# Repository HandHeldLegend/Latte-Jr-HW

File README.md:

# Latte Project
This is the official Github page for project Latte Jr from Hand Held Legend.

## Software and PCB License
<br />This firmware and PCB model are licensed under a <a rel="license" href="http://creativecommons.org/licenses/by-nc-sa/3.0/">Creative Commons Attribution-NonCommercial-ShareAlike 3.0 Unported License</a>.

## 3D Models License

<br />The 3D shell, buttons, and other associated models are licensed under a <a rel="license" href="http://creativecommons.org/licenses/by/4.0/">Creative Commons Attribution 4.0 International License</a>.

## Attributions

Resources Cross-Referenced for shell shape:
- 3D Scans by Wesk

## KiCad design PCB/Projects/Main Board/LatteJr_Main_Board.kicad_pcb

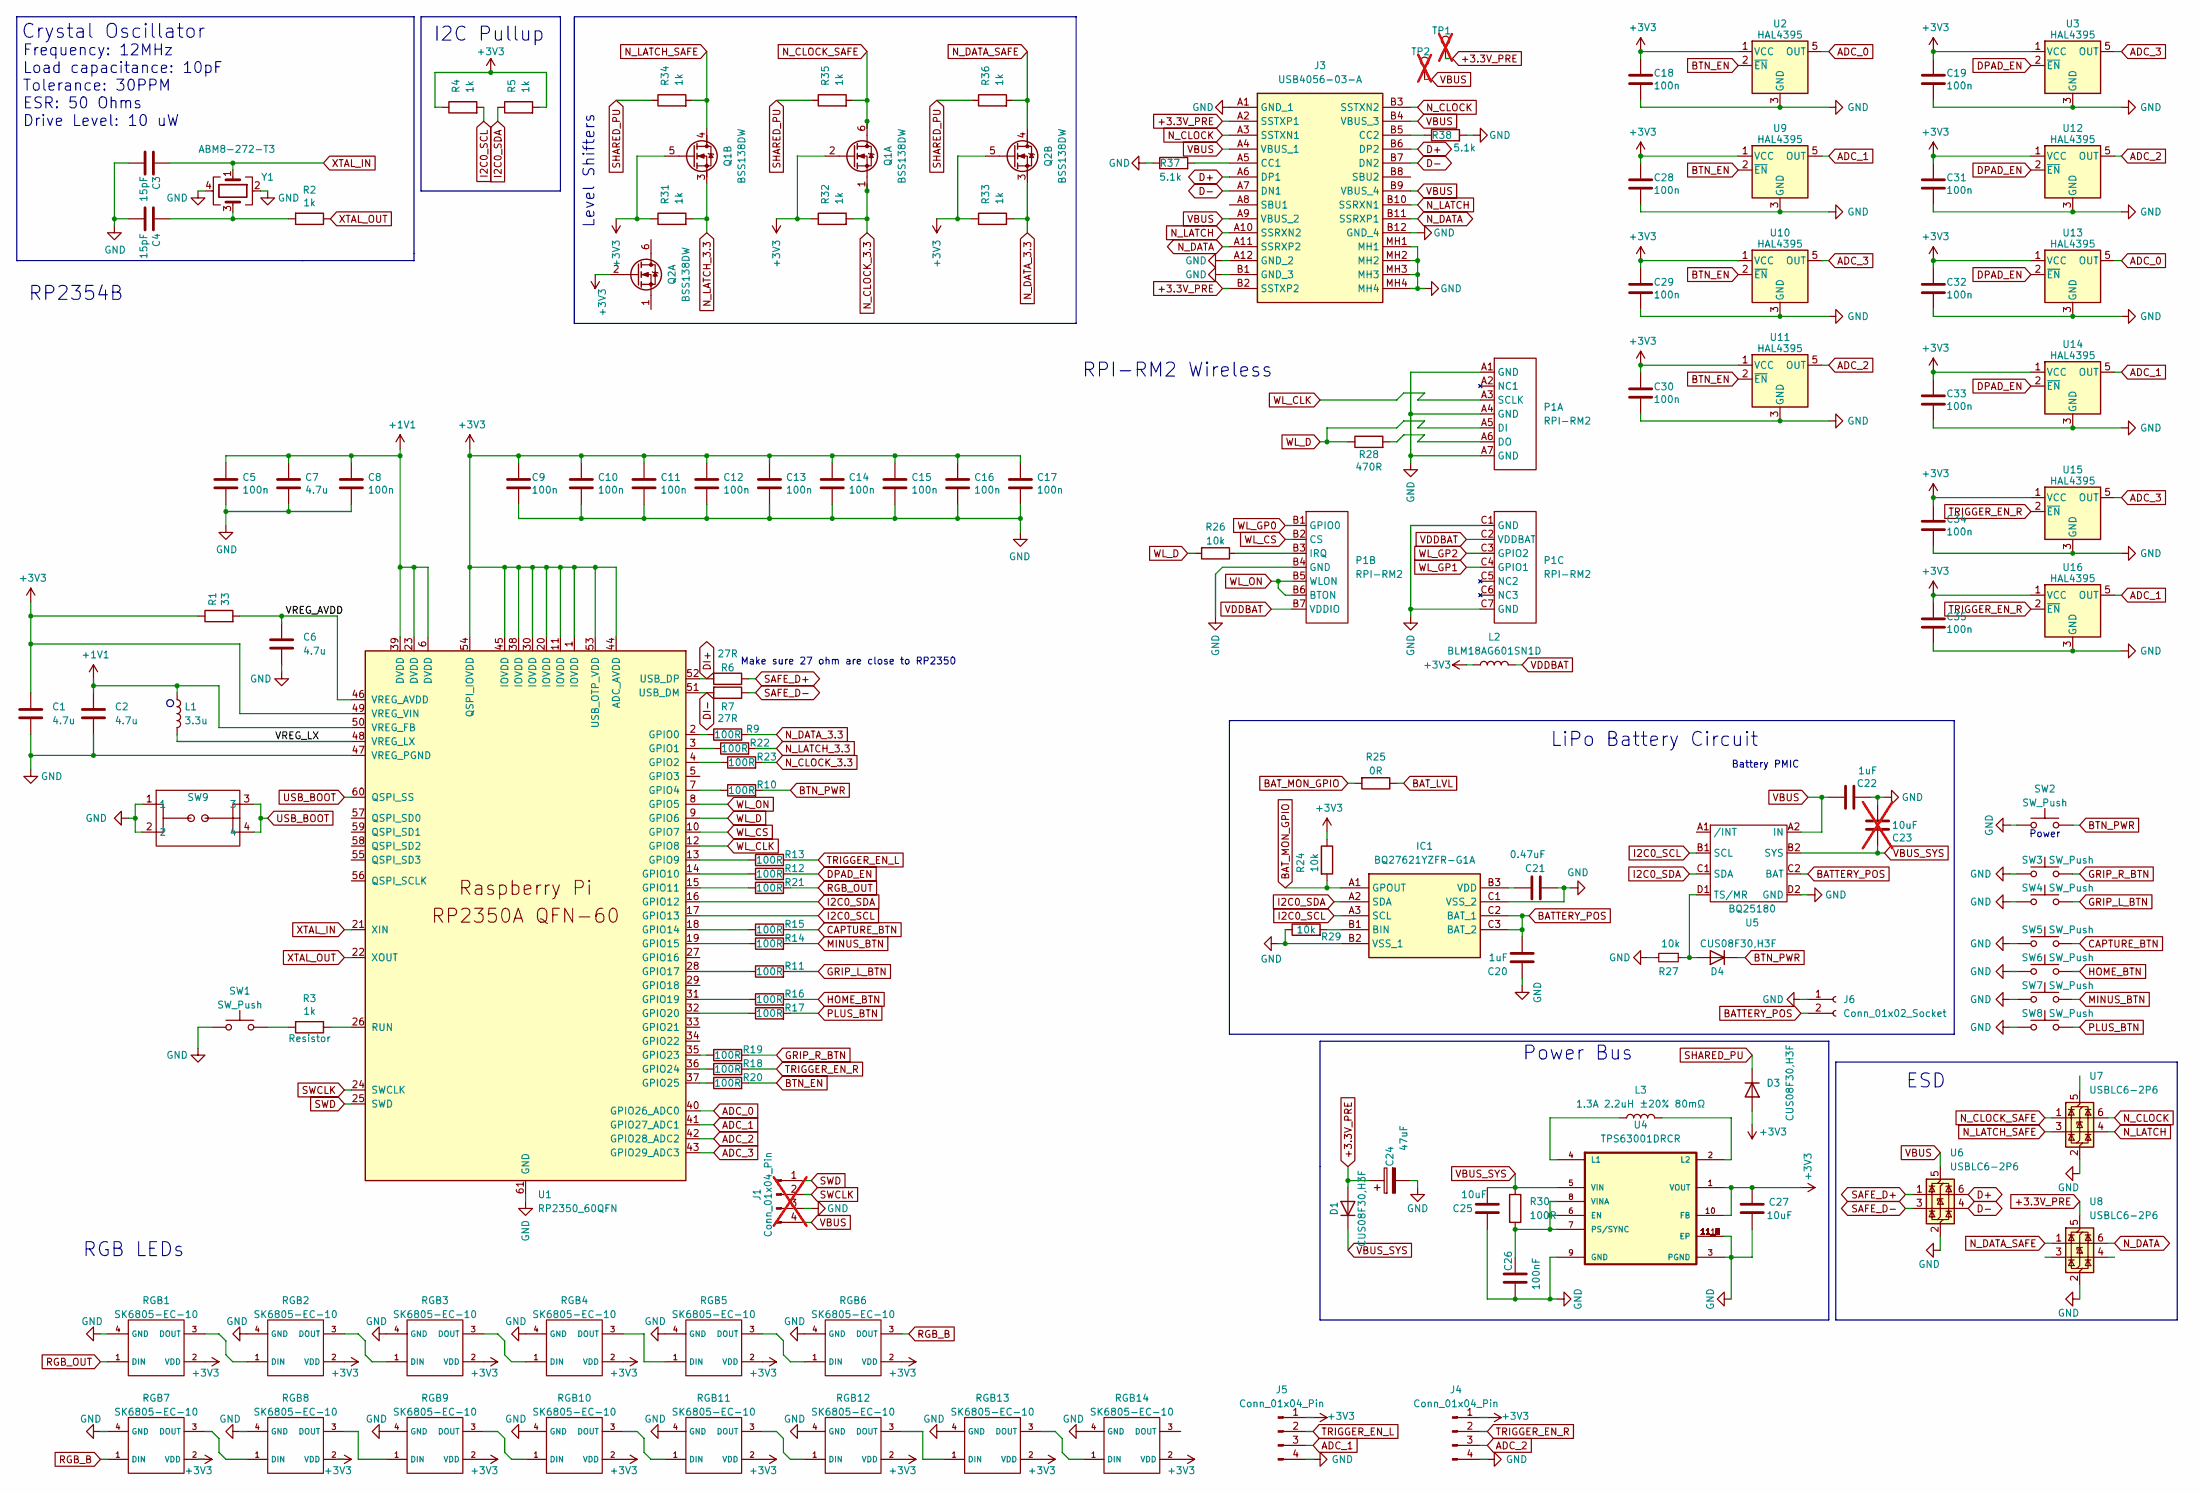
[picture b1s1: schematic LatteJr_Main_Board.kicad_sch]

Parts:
C1, C2, C6, C7: 4.7u; C_0402_1005Metric; MPN CL05A475KP5NRNC; LCSC C368809
C3, C4: 15pF; C_0402_1005Metric; MPN CC0402FRNPO9BN150; LCSC C326803
C5, C8, C9, C10, C11, C12, C13, C14, C15, C16, C17, C18, C19, C28, C29, C30, C31, C32, C33, C34, C35: 100n; C_0201_0603Metric; MPN GRM033R61A104KE15D; LCSC C76934
C20, C22: 1uF; C_0201_0603Metric; MPN GRM033R60J105KEA2D; LCSC C76929
C21: 0.47uF; C_0201_0603Metric; MPN GRM033R60J474KE90D; LCSC C85926
C23: 10uF; C_0805_2012Metric; MPN CL21A106KPFNNNE; LCSC C17024; not fitted
C24: 47uF; CP_EIA-3216-18_Kemet-A; MPN TAJA476K006RNJ; LCSC C7190
C25, C27: 10uF; C_0805_2012Metric; MPN CL21A106KPFNNNE; LCSC C17024
C26: 100nF; C_0201_0603Metric; MPN CL03A104KQ3NNNC; LCSC C160831
D1, D3, D4: CUS08F30,H3F; D_SOD-323_HandSoldering; MPN CUS08F30,H3F; LCSC C150183
IC1: BQ27621YZFR-G1A; BGA9C50P3X3_162X158X62; Mouser Part Number 595-BQ27621YZFR-G1A
J1: Conn_01x04_Pin; PinHeader_1x04_P2.00mm_Vertical; not fitted
J3: USB4056-03-A; USB405603A; Mouser Part Number 640-USB4056-03-A
J4, J5: Conn_01x04_Pin; 5051100492; MPN 5051100492; LCSC C588007
J6: Conn_01x02_Socket; Molex_PicoBlade_53048-0210_1x02_P1.25mm_Horizontal; MPN 530480210; LCSC C505099
L1: 3.3u; L_pol_2016; MPN AOTA-B201610S3R3-101-T; LCSC C42411119
L2: BLM18AG601SN1D; L_0603_1608Metric; MPN BLM18AG601SN1D; LCSC C19330
L3: 1.3A 2.2uH ±20% 80mΩ; L_1008_2520Metric; MPN MIP25202R2MBE; LCSC C315721
P1: RPI-RM2; RPI_RM2; MPN RPI-RM2
Q1, Q2: BSS138DW; SOT-363_SC-70-6; MPN BSS138DW-7-F; LCSC C154900
R1: 33; R_0201_0603Metric; MPN RC0201FR-0733RL; LCSC C295794
R2, R3, R4, R5, R31, R32, R33, R34, R35, R36: 1k; R_0201_0603Metric; MPN RC0201FR-071KL; LCSC C138165
R6, R7: 27R; R_0201_0603Metric; MPN RC0201FR-0727RL; LCSC C273268
R9, R10, R11, R12, R13, R14, R15, R16, R17, R18, R19, R20, R21, R22, R23, R30: 100R; R_0201_0603Metric; MPN RC0201FR-07100RL; LCSC C77623
R24, R26, R27, R29: 10k; R_0201_0603Metric; MPN RC0201FR-0710KL; LCSC C106225
R25: 0R; R_0201_0603Metric; MPN RC0201FR-070RL; LCSC C106227
R28: 470R; R_0201_0603Metric; MPN AC0201FR-07470RL; LCSC C226558
R37, R38: 5.1k; R_0201_0603Metric; MPN RC0201FR-075K1L; LCSC C274341
RGB1, RGB2, RGB3, RGB4, RGB5, RGB6, RGB7, RGB8, RGB9, RGB10, RGB11, RGB12, RGB13, RGB14: SK6805-EC-10; MPN SK6805-EC-10; LCSC C22394946
SW1, SW2, SW3, SW4, SW5, SW6, SW7, SW8: SW_Push; KSC-TE; MPN KSC201J LFS; LCSC C221725
SW9: 1TS026A-1000-0550; MPN 1TS026A-1000-0550; LCSC C913778
TP1, TP2: TestPoint; TestPoint_Pad_D1.0mm; not fitted
U1: RP2350_60QFN; RP2350-QFN-60-1EP_7x7_P0.4mm_EP3.4x3.4mm_ThermalVias; MPN RP2354A; LCSC C41378174
U2, U3, U9, U10, U11, U12, U13, U14, U15, U16: HAL4395; SOT-23-5L; MPN HAL4395SO5; LCSC C49165022
U4: TPS63001DRCR; VREG_V62_16624-01YE; MPN TPS63001DRCR; LCSC C28060
U5: BQ25180; DSBGA; MPN BQ25180YBGR; LCSC C3682423
U6, U7, U8: USBLC6-2P6; SOT-666; MPN USBLC6-2P6; LCSC C2827693
Y1: ABM8-272-T3; Crystal_SMD_3225-4Pin_3.2x2.5mm; MPN ABM8-272-T3; LCSC C20625731

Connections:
+1V1: C2.1, C5.1, C7.1, C8.1, L1.1, U1.6 (DVDD), U1.23 (DVDD), U1.39 (DVDD), U1.50 (VREG_FB)
+3.3V_PRE: C24.1, D1.2 (A), J3.A2 (SSTXP1), J3.B2 (SSTXP2), TP1.1, U8.5 (VBUS)
+3V3: C1.1, C9.1, C10.1, C11.1, C12.1, C13.1, C14.1, C15.1, C16.1, C17.1, C18.1, C19.1, C27.1, C28.1, C29.1, C30.1, C31.1, C32.1, C33.1, C34.1, C35.1, D3.2 (A), J4.1, J5.1, L2.1, Q1.2 (G1), Q1.5 (G2), Q2.2 (G1), Q2.5 (G2), R1.1, R4.1, R5.2, R24.1, R31.1, R32.1, R33.1, RGB1.2 (VDD), RGB2.2 (VDD), RGB3.2 (VDD), RGB4.2 (VDD), RGB5.2 (VDD), RGB6.2 (VDD), RGB7.2 (VDD), RGB8.2 (VDD), RGB9.2 (VDD), RGB10.2 (VDD), RGB11.2 (VDD), RGB12.2 (VDD), RGB13.2 (VDD), RGB14.2 (VDD), U1.1 (IOVDD), U1.11 (IOVDD), U1.20 (IOVDD), U1.30 (IOVDD), U1.38 (IOVDD), U1.44 (ADC_AVDD), U1.45 (IOVDD), U1.49 (VREG_VIN), U1.53 (USB_OTP_VDD), U1.54 (QSPI_IOVDD), U2.1 (VCC), U3.1 (VCC), U4.1 (VOUT), U4.10 (FB), U9.1 (VCC), U10.1 (VCC), U11.1 (VCC), U12.1 (VCC), U13.1 (VCC), U14.1 (VCC), U15.1 (VCC), U16.1 (VCC)
/VREG_AVDD: C6.1, R1.2, U1.46 (VREG_AVDD)
/VREG_LX: L1.2, U1.48 (VREG_LX)
ADC_0: U1.40 (GPIO26_ADC0), U2.5 (OUT), U13.5 (OUT)
ADC_1: J5.3, U1.41 (GPIO27_ADC1), U9.5 (OUT), U14.5 (OUT), U16.5 (OUT)
ADC_2: J4.3, U1.42 (GPIO28_ADC2), U11.5 (OUT), U12.5 (OUT)
ADC_3: U1.43 (GPIO29_ADC3), U3.5 (OUT), U10.5 (OUT), U15.5 (OUT)
BATTERY_POS: C20.2, IC1.C2 (BAT_1), IC1.C3 (BAT_2), J6.2, U5.C2 (BAT)
BAT_LVL: R25.1
BAT_MON_GPIO: IC1.A1 (GPOUT), R24.2, R25.2
BTN_EN: R20.2, U2.2 (~EN), U9.2 (~EN), U10.2 (~EN), U11.2 (~EN)
BTN_PWR: D4.1 (K), R10.2, SW2.2
CAPTURE_BTN: R15.2, SW5.2
D+: J3.A6 (DP1), J3.B6 (DP2), U6.6 (I/O1)
D-: J3.A7 (DN1), J3.B7 (DN2), U6.4 (I/O2)
DI+: R6.2, U1.52 (USB_DP)
DI-: R7.2, U1.51 (USB_DM)
DPAD_EN: R12.2, U3.2 (~EN), U12.2 (~EN), U13.2 (~EN), U14.2 (~EN)
GND: C1.2, C2.2, C3.2, C4.2, C5.2, C6.2, C7.2, C8.2, C9.2, C10.2, C11.2, C12.2, C13.2, C14.2, C15.2, C16.2, C17.2, C18.2, C19.2, C20.1, C21.2, C22.2, C23.1, C24.2, C25.1, C26.1, C27.2, C28.2, C29.2, C30.2, C31.2, C32.2, C33.2, C34.2, C35.2, IC1.B2 (VSS_1), IC1.C1 (VSS_2), J1.3, J3.A1 (GND_1), J3.A12 (GND_2), J3.B1 (GND_3), J3.B12 (GND_4), J3.MH1, J3.MH2, J3.MH3, J3.MH4, J4.4, J5.4, J6.1, P1.A1 (GND), P1.A4 (GND), P1.A7 (GND), P1.B4 (GND), P1.C1 (GND), P1.C7 (GND), R27.2, R29.1, R37.1, R38.2, RGB1.4 (GND), RGB2.4 (GND), RGB3.4 (GND), RGB4.4 (GND), RGB5.4 (GND), RGB6.4 (GND), RGB7.4 (GND), RGB8.4 (GND), RGB9.4 (GND), RGB10.4 (GND), RGB11.4 (GND), RGB12.4 (GND), RGB13.4 (GND), RGB14.4 (GND), SW1.1, SW2.1, SW3.1, SW4.1, SW5.1, SW6.1, SW7.1, SW8.1, SW9.1, SW9.2, U1.47 (VREG_PGND), U1.61 (GND), U2.3 (GND), U3.3 (GND), U4.3 (PGND), U4.9 (GND), U4.11 (EP), U4.11_1 (EP), U4.11_2 (EP), U4.11_3 (EP), U4.11_4 (EP), U4.11_5 (EP), U4.11_6 (EP), U4.11_7 (EP), U4.11_8 (EP), U5.D2 (GND), U6.2 (GND), U7.2 (GND), U8.2 (GND), U9.3 (GND), U10.3 (GND), U11.3 (GND), U12.3 (GND), U13.3 (GND), U14.3 (GND), U15.3 (GND), U16.3 (GND), Y1.2, Y1.4
GRIP_L_BTN: R11.2, SW4.2
GRIP_R_BTN: R19.2, SW3.2
HOME_BTN: R16.2, SW6.2
I2C0_SCL: IC1.A3 (SCL), R4.2, U1.17 (GPIO13), U5.B1 (SCL)
I2C0_SDA: IC1.A2 (SDA), R5.1, U1.16 (GPIO12), U5.C1 (SDA)
MINUS_BTN: R14.2, SW7.2
N_CLOCK: J3.A3 (SSTXN1), J3.B3 (SSTXN2), U7.6 (I/O1)
N_CLOCK_3.3: Q1.1 (S1), R23.2, R32.2
N_CLOCK_SAFE: Q1.6 (D1), R35.2, U7.1 (I/O1)
N_DATA: J3.A11 (SSRXP2), J3.B11 (SSRXP1), U8.6 (I/O1)
N_DATA_3.3: Q2.3 (D2), R9.2, R33.2
N_DATA_SAFE: Q2.4 (S2), R36.2, U8.1 (I/O1)
N_LATCH: J3.A10 (SSRXN2), J3.B10 (SSRXN1), U7.4 (I/O2)
N_LATCH_3.3: Q1.3 (D2), R22.2, R31.2
N_LATCH_SAFE: Q1.4 (S2), R34.2, U7.3 (I/O2)
unnamed: C4.1, R2.2, Y1.3
unnamed: D4.2 (A), R27.1, U5.D1 (TS/MR)
unnamed: IC1.B1 (BIN), R29.2
unnamed: C21.1, IC1.B3 (VDD)
unnamed: J3.A5 (CC1), R37.2
unnamed: J3.B5 (CC2), R38.1
unnamed: P1.A6 (DO), R28.2
unnamed: P1.B3 (IRQ), R26.1
unnamed: R3.2, SW1.2
unnamed: RGB1.3 (DOUT), RGB2.1 (DIN)
unnamed: RGB2.3 (DOUT), RGB3.1 (DIN)
unnamed: RGB3.3 (DOUT), RGB4.1 (DIN)
unnamed: RGB4.3 (DOUT), RGB5.1 (DIN)
unnamed: RGB5.3 (DOUT), RGB6.1 (DIN)
unnamed: RGB7.3 (DOUT), RGB8.1 (DIN)
unnamed: RGB8.3 (DOUT), RGB9.1 (DIN)
unnamed: RGB9.3 (DOUT), RGB10.1 (DIN)
unnamed: RGB10.3 (DOUT), RGB11.1 (DIN)
unnamed: RGB11.3 (DOUT), RGB12.1 (DIN)
unnamed: RGB12.3 (DOUT), RGB13.1 (DIN)
unnamed: RGB13.3 (DOUT), RGB14.1 (DIN)
unnamed: R9.1, U1.2 (GPIO0)
unnamed: R22.1, U1.3 (GPIO1)
unnamed: R23.1, U1.4 (GPIO2)
unnamed: R10.1, U1.7 (GPIO4)
unnamed: R13.1, U1.13 (GPIO9)
unnamed: R12.1, U1.14 (GPIO10)
unnamed: R21.1, U1.15 (GPIO11)
unnamed: R15.1, U1.18 (GPIO14)
unnamed: R14.1, U1.19 (GPIO15)
unnamed: R11.1, U1.28 (GPIO17)
unnamed: R16.1, U1.31 (GPIO19)
unnamed: R17.1, U1.32 (GPIO20)
unnamed: R19.1, U1.35 (GPIO23)
unnamed: R18.1, U1.36 (GPIO24)
unnamed: R20.1, U1.37 (GPIO25)
unnamed: R3.1, U1.26 (RUN)
unnamed: C26.2, R30.2, U4.6 (EN), U4.7 (PS/SYNC), U4.8 (VINA)
unnamed: L3.1, U4.4 (L1)
unnamed: L3.2, U4.2 (L2)
PLUS_BTN: R17.2, SW8.2
RGB_B: RGB6.3 (DOUT), RGB7.1 (DIN)
RGB_OUT: R21.2, RGB1.1 (DIN)
SAFE_D+: R6.1, U6.1 (I/O1)
SAFE_D-: R7.1, U6.3 (I/O2)
SHARED_PU: D3.1 (K), R34.1, R35.1, R36.1
SWCLK: J1.2, U1.24 (SWCLK)
SWD: J1.1, U1.25 (SWD)
TRIGGER_EN_L: J5.2, R13.2
TRIGGER_EN_R: J4.2, R18.2, U15.2 (~EN), U16.2 (~EN)
USB_BOOT: SW9.3, SW9.4, U1.60 (QSPI_SS)
VBUS: C22.1, J1.4, J3.A4 (VBUS_1), J3.A9 (VBUS_2), J3.B4 (VBUS_3), J3.B9 (VBUS_4), TP2.1, U5.A2 (IN), U6.5 (VBUS)
VBUS_SYS: C23.2, C25.2, D1.1 (K), R30.1, U4.5 (VIN), U5.B2 (SYS)
VDDBAT: L2.2, P1.B7 (VDDIO), P1.C2 (VDDBAT)
WL_CLK: P1.A3 (SCLK), U1.12 (GPIO8)
WL_CS: P1.B2 (CS), U1.10 (GPIO7)
WL_D: P1.A5 (DI), R26.2, R28.1, U1.9 (GPIO6)
WL_GP0: P1.B1 (GPIO0)
WL_GP1: P1.C4 (GPIO1)
WL_GP2: P1.C3 (GPIO2)
WL_ON: P1.B5 (WLON), P1.B6 (BTON), U1.8 (GPIO5)
XTAL_IN: C3.1, U1.21 (XIN), Y1.1
XTAL_OUT: R2.1, U1.22 (XOUT)

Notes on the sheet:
Power
ESD
RP2354B
RGB LEDs
RPI-RM2 Wireless
Crystal Oscillator
Level Shifters
I2C Pullup
Frequency: 12MHz Load capacitance: 10pF Tolerance: 30PPM ESR: 50 Ohms Drive Level: 10 uW
Power Bus
Make sure 27 ohm are close to RP2350
Battery PMIC
LiPo Battery Circuit

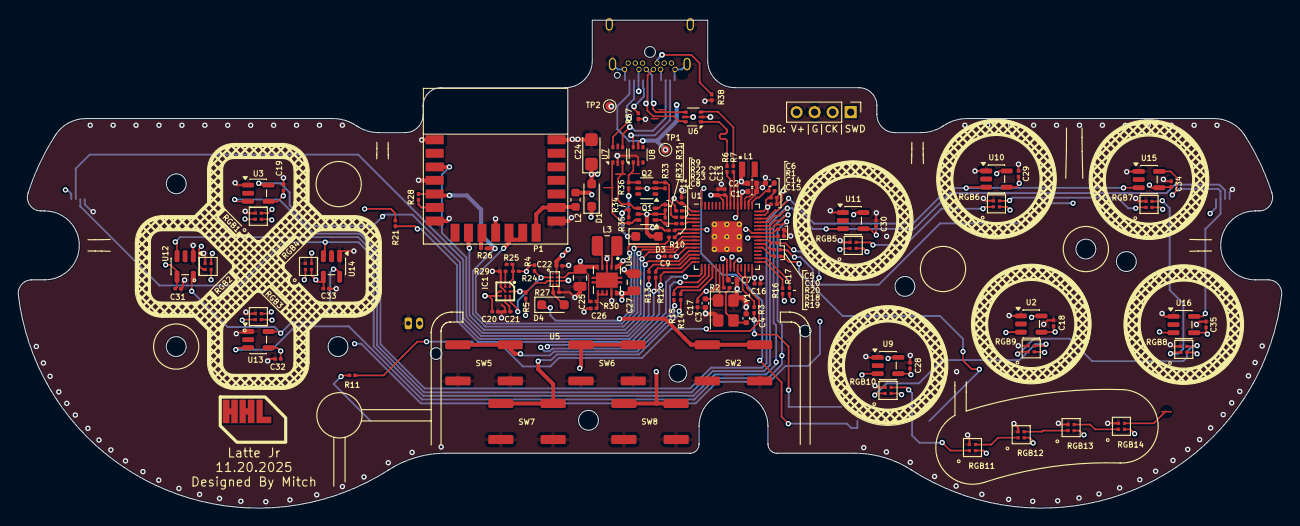
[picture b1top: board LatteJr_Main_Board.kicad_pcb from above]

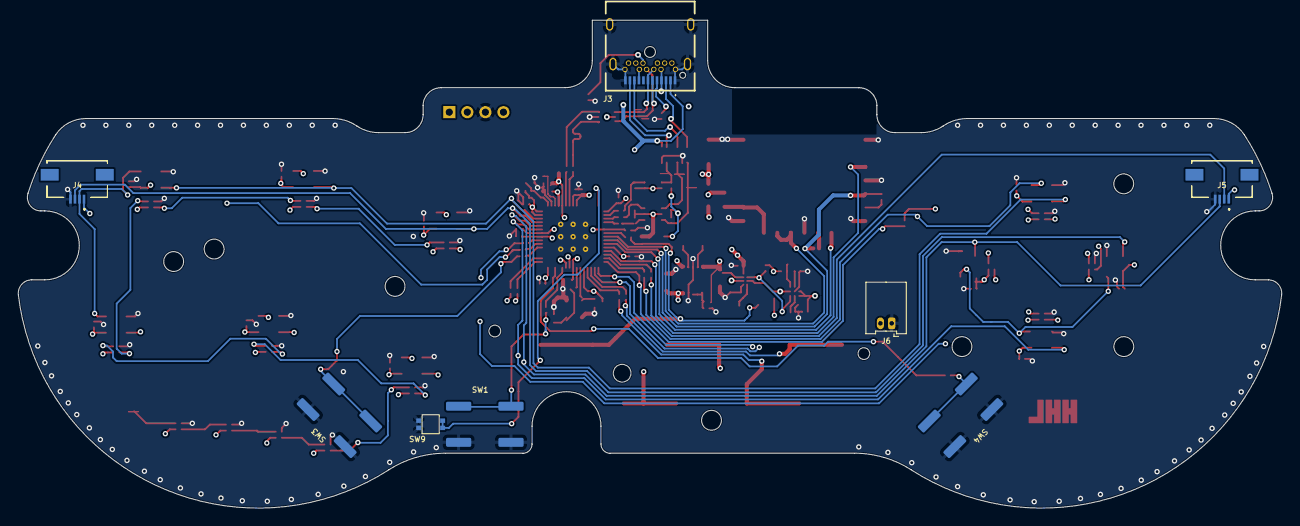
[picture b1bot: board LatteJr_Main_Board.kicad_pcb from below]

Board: 4 copper layers, 140.0 x 54.0 mm, 128 parts (8 on the bottom side), 95 nets.

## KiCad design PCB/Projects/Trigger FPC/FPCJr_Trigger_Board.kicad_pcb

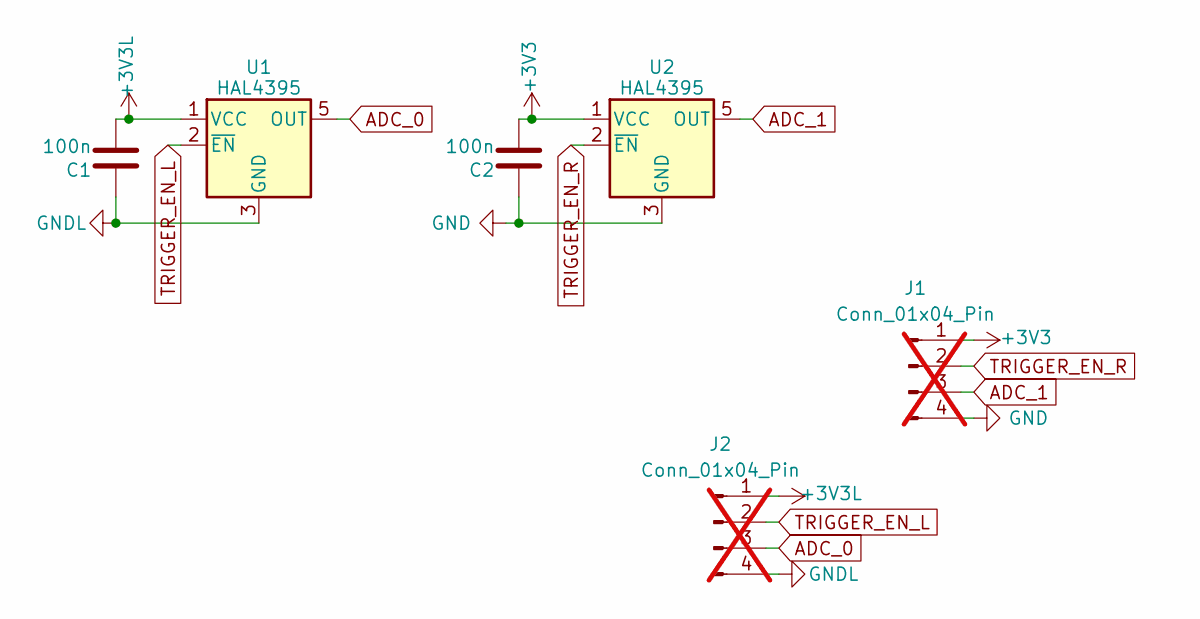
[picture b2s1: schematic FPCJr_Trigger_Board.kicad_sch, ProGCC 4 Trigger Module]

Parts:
C1, C2: 100n; C_0201_0603Metric; MPN GRM033R61A104KE15D; LCSC C76934
J1, J2: Conn_01x04_Pin; 505110-0492 Ribbon; not fitted
U1, U2: HAL4395; SOT-23-5L; MPN HAL4395SO5; LCSC C49165022

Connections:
+3V3: C2.2, J1.1, U2.1 (VCC)
+3V3L: C1.2, J2.1, U1.1 (VCC)
ADC_0: J2.3, U1.5 (OUT)
ADC_1: J1.3, U2.5 (OUT)
GND: C2.1, J1.4, U2.3 (GND)
GNDL: C1.1, J2.4, U1.3 (GND)
TRIGGER_EN_L: J2.2, U1.2 (~EN)
TRIGGER_EN_R: J1.2, U2.2 (~EN)

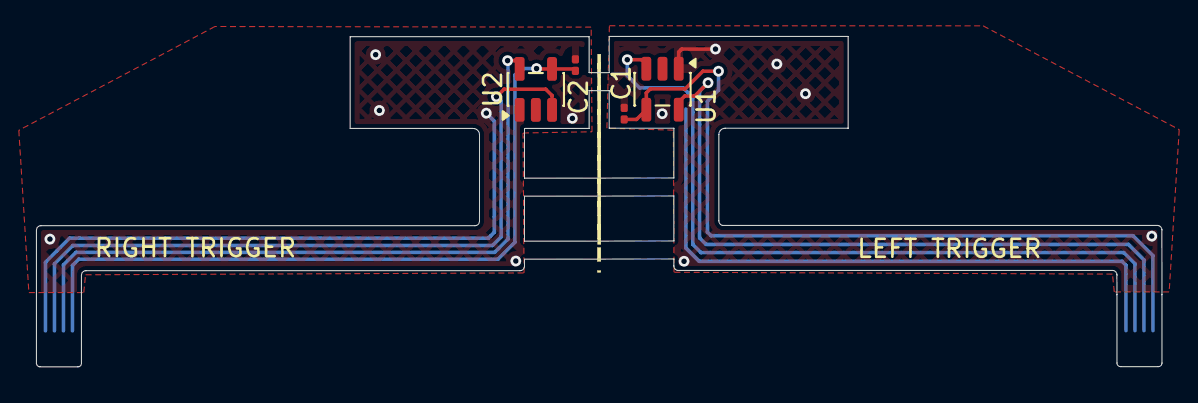
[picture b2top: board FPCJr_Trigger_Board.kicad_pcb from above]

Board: 2 copper layers, 62.5 x 18.4 mm, 6 parts (0 on the bottom side), 8 nets.

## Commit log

2025-11-18 Add a blank file
2025-11-19 Some Routing
2025-11-19 Routing
2025-11-19 Main Board Routing
2025-11-20 Update PCB
2025-11-20 Flex PCB
2025-11-20 Prod
2025-11-20 Printables
2025-12-12 FPC fixes
2026-01-03 FPC Board Update
2026-01-14 PCBs updated
2026-01-18 BOOT button placement
